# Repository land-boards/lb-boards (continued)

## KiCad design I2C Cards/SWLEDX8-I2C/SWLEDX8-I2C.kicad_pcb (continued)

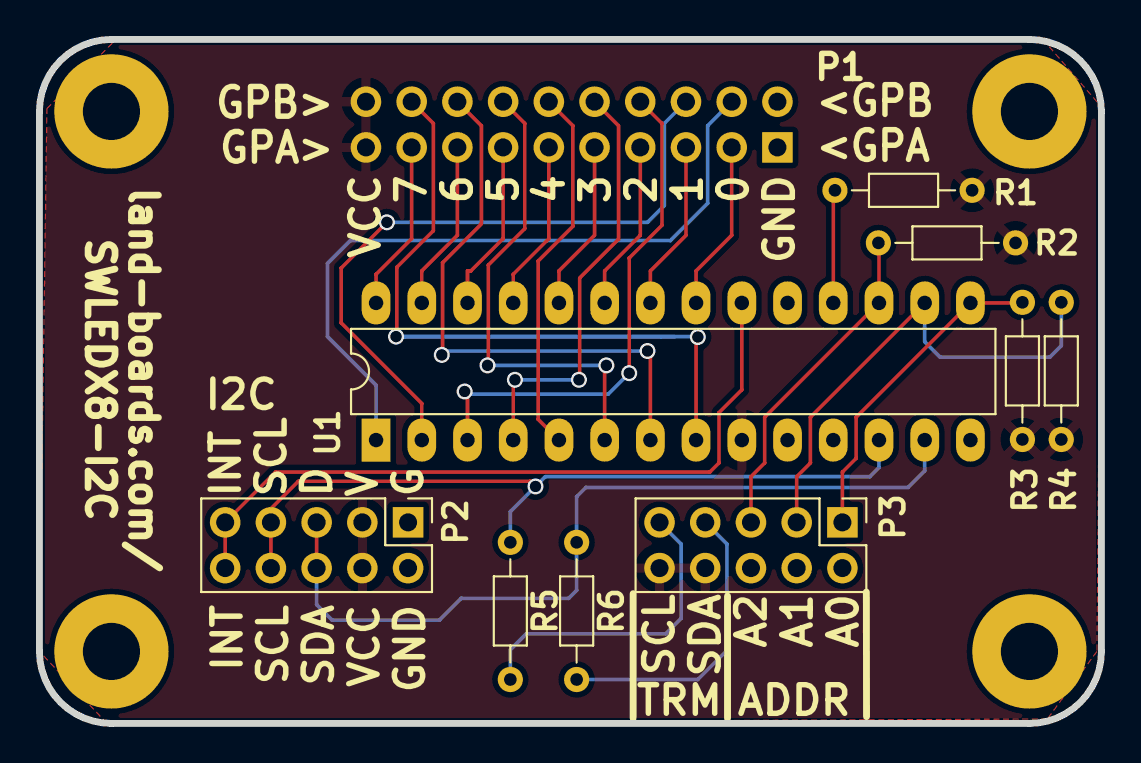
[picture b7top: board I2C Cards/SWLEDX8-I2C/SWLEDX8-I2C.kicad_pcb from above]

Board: 2 copper layers, 59.0 x 38.0 mm, 15 parts (1 on the bottom side), 27 nets.

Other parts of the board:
TEST: COUPON; TEST_BLK-REAR
